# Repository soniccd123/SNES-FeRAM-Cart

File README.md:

# SNES FeRAM Cart
A Open Hardware SNES Cartridge with save capability

# What is that?
A repro cartridge PCB for SNES and Super Famicom consoles compatible with LoROM and HiROM software and save capability using FeRAM memory. Its a open hardware project and can be modified with no restriction

This project was possible thanks to poorstudenthobbyist (Very nice and informative guides) and whicker (Showed the basics of how to wire a FeRAM to SNES), as well as other members of NESdev forums.

# Why is that?
While there are very nice comercially available repro PCB solutions, these are closed solutions that often doesn't fit the needs of everyone, specially concerning availability of parts, so, making this project open is not only a way to give back to the community that helped me alot, but also to give the ones that need a more versitile way to solve their problems. I know that the way that this PCB was designed may not fit everyone, but i hope that the ability to modify this project as one needs solves this.

I also find the canibalization of original cartridges for making repros, while understandable in many cases, discusting, so, may this project help to curb this practice.

# Features as of now
- Suports SNES and Super Famicom
- ROM Support for up to 4MB
- HiROM and LoROM software (set by jumpers)
- 32KB of FeRAM for saving (256kb)
- No need for backup battery
- Rudimentary ROM bank switch (Permits multiple games on same ROM)
- SuperCIC support
- DOES NOT SUPPORT SPECIAL CHIP GAMES (while i would love to, this is quite away from my capacity as of now)

# Component List:
- 1x FM1808B;
- 1x 27C322 (May use other 27CXX memories with some minor modifications);
- 1x 74HC139 (or LS);
- 1x 4081;
- 1x 4071;
- 2x 74HC245;
- 1x SuperCIC (PIC12F629 model);
- 1x Led (Optional, only used for SuperCIC)
- 4x 1K Resistors (5x if using the LED with the SuperCIC);
- 1x 4 channel DIP Switch;
- 2x 10nF Capacitors;

# Technical details

This project was developed using KiCAD and can be easily modified and studied by using it. Terminals are left in the PCB for all cartridge port connections for testing, but these can easily be removed if wanted.

4081 and 4071 circuitry help to control backup RAM access and also permit FeRAM correctly reading and writing. If

While bank switching is present, its use is not absolutely required for the cart to work. In this case, the resistors are not needed, just short each SW1 channel (as if it were on). 

Also, while save capability is present, it is not required for the cart to work. 4071 and 4081 are still required in these cases

SuperCIC have been tested by other users and works. A SOIC8 footprint will be added aswell in the next commit for more package options.

# How to use

The ROMs to be written to the EPROM need to be headerless.

ROM type: HiROM and LoROM are selected by shorting the corresponding side of all the jumpers to the center, HiROM ones are annotated with H and LoROM with L.

Bank Switching: The user may write multiple roms to the same EPROM, the DIP switch controls which area of the EPROM is read by the SNES/Super Famicom; The minimum bank size is 256KB. Each of the switches connect a memory address line between the system and the EPROM: when the switch is on, the respective address line is controlled by the SNES; When off, the EPROM adress line is pulled-up and cut from SNES control. the address lines are A20, A19, A18, A17 (considering LSB as A0). To select the desired bank, turn the switches on and off acordingly to the begining address that the ROM occupies in the EPROM.

Examples:

ROM_x begin at 0x100000 -> Switch just A19 off (pull-up);           
ROM_y begin at 0x180000 -> Switch A19 and A18 off;

This technique may not be compatible with save supporting SNES/Super Famicom software.

How to make multirom file: Just use the CMD command "copy /b rom_x.bin + rom_y.bin + rom_z.bin rom_result.bin" to join them to one file. One may join how many ROMs he wants to, just be shure that the result file is smaller than the total size of the EPROM and that the ROMs fit correctly to each desired bank to make software switching possible.

# Disclaimer

I'm not an professional engineer and created this project as a hobby, this said, problems and errors maybe present and in need to be corrected. I'll try you to help the best as I can if any problems arrise but be aware that they may exist.

Happy playing!

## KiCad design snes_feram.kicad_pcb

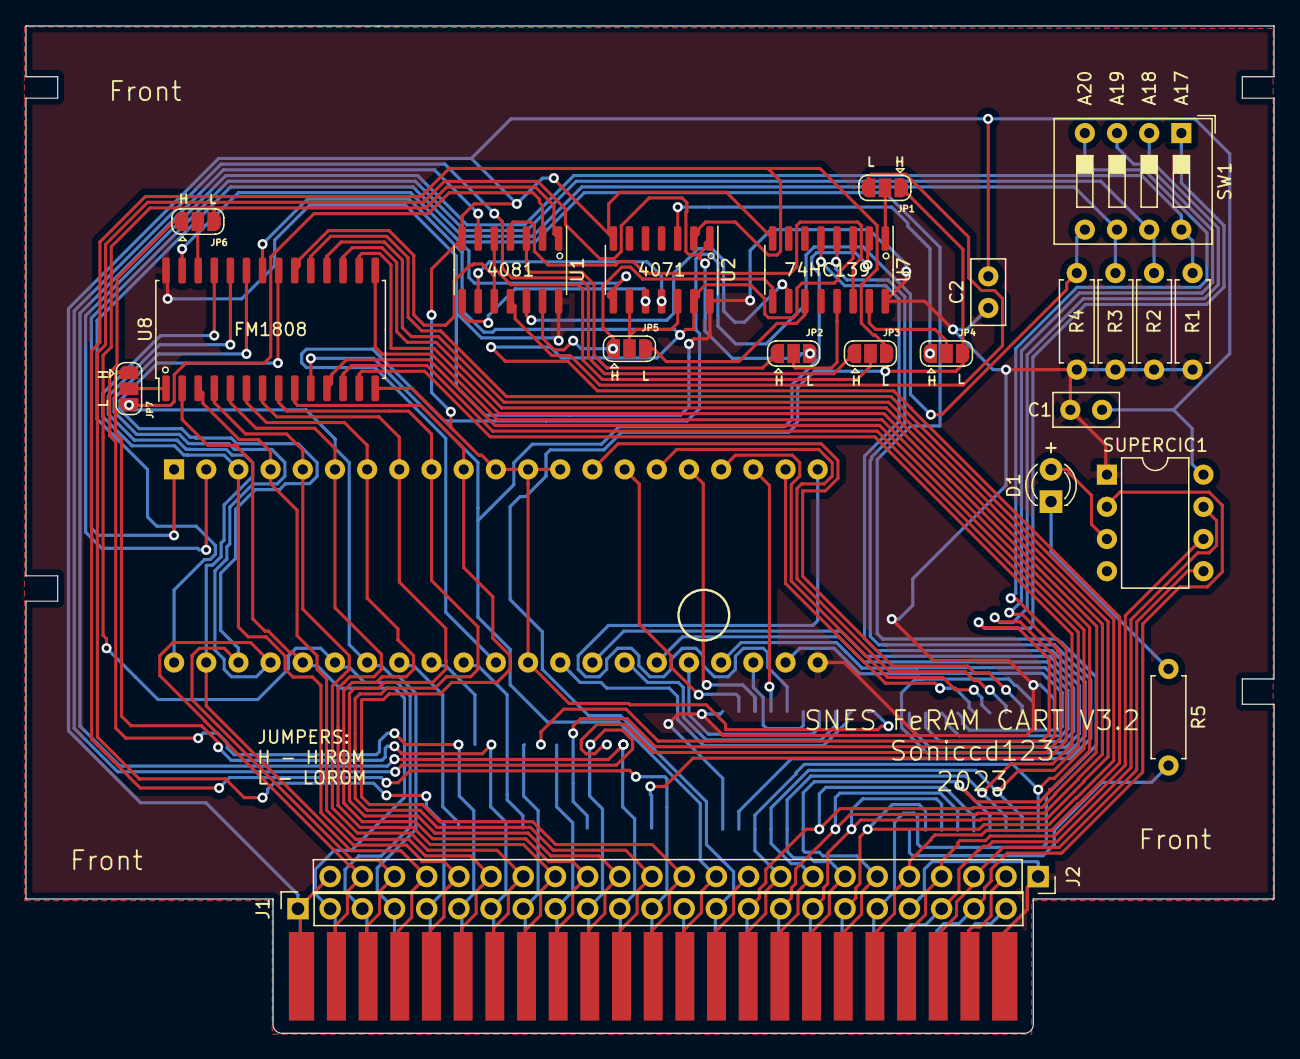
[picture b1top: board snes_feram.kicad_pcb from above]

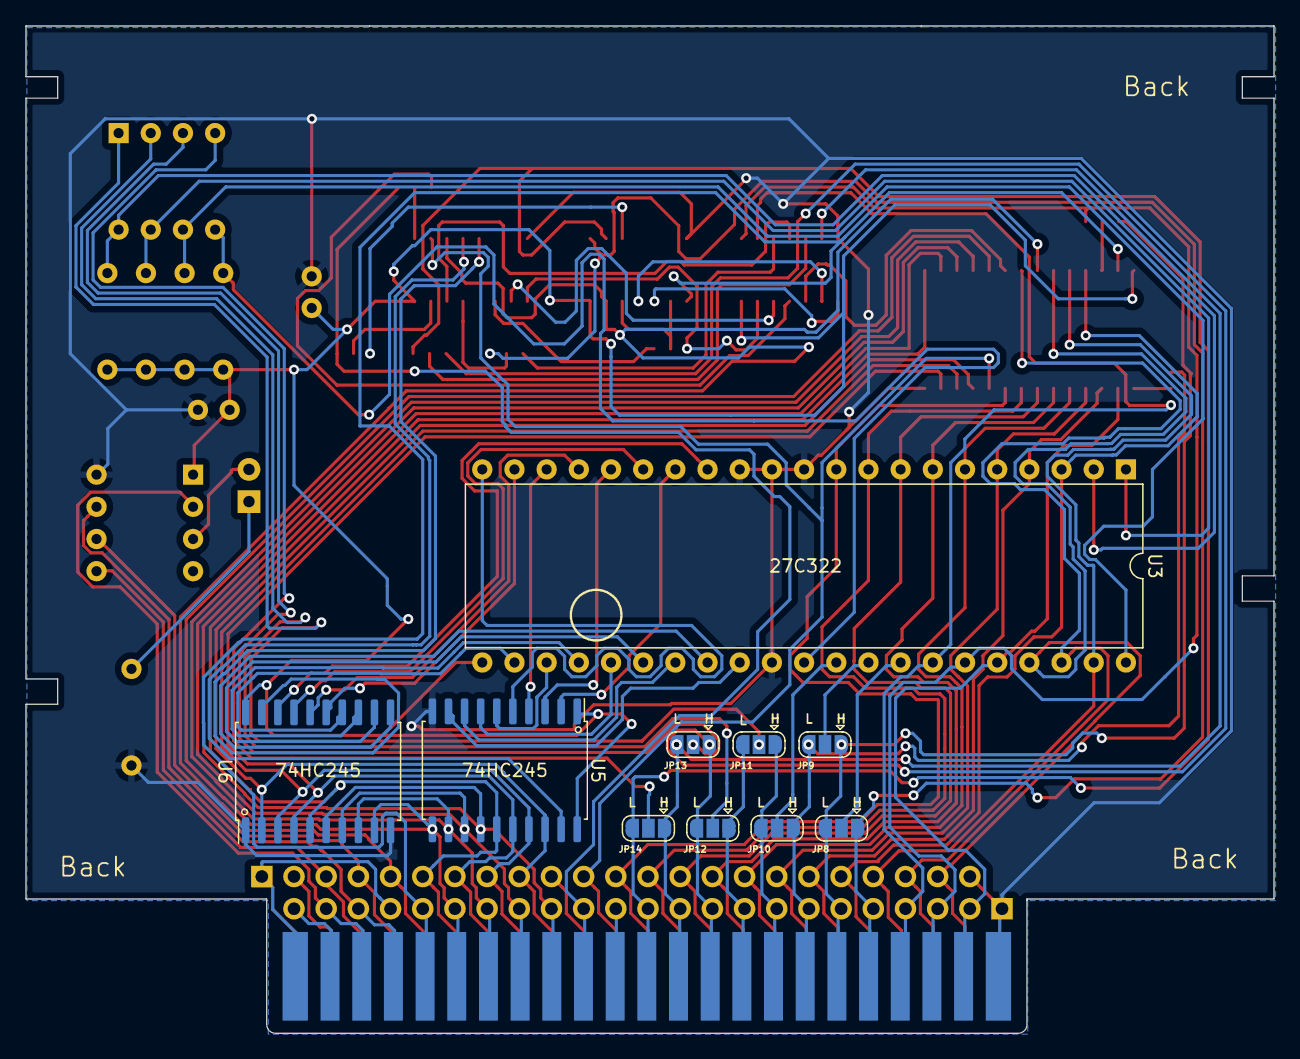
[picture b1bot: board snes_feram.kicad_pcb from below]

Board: 2 copper layers, 98.5 x 79.5 mm, 34 parts (10 on the bottom side), 90 nets.

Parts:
C1, C2: C; C_Disc_D5.0mm_W2.5mm_P2.50mm
CON1: SNES-EDGE; SNES-EDGE-Bigger
D1: LED; LED_D3.0mm
J1, J2: Conn_01x23_Male; PinSocket_1x23_P2.54mm_Vertical
JP1, JP2, JP3, JP4, JP5, JP6, JP7, JP8, JP9, JP10, JP11, JP12, JP13, JP14: SolderJumper_3_Open; SolderJumper-3_P1.3mm_Open_RoundedPad1.0x1.5mm
R1, R2, R3, R4: R; R_Axial_DIN0207_L6.3mm_D2.5mm_P7.62mm_Horizontal
R5: 1K; R_Axial_DIN0207_L6.3mm_D2.5mm_P7.62mm_Horizontal
SUPERCIC1: PIC12F629-IMC; DIP-8_W7.62mm
SW1: SW_DIP_x04; SW_DIP_SPSTx04_Slide_9.78x12.34mm_W7.62mm_P2.54mm
U1: 4081; SOIC-14_3.9x8.7mm_P1.27mm
U2: 4071; SOIC-14_3.9x8.7mm_P1.27mm
U3: 27C322; DIP-42_W15.24mm
U5, U6: 74LS245; SOIC-20W_7.5x12.8mm_P1.27mm
U7: 74LS139; SOIC-16_3.9x9.9mm_P1.27mm
U8: FM18W08-SG; SOIC-28W_7.5x17.9mm_P1.27mm

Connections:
+5V: C1.1, C2.1, CON1.27, CON1.58, J1.20, J2.1, R1.1, R2.1, R3.1, R4.1, SUPERCIC1.1 (VDD), U1.14 (VDD), U2.14 (VDD), U3.22 (VCC), U5.1 (A->B), U5.20 (VCC), U6.20 (VCC), U7.16 (VCC), U8.28 (VDD)
/A0: CON1.16, J2.12, U3.10 (A0), U8.9 (A1)
/A1: CON1.15, J2.13, U3.9 (A1), U8.8 (A2)
/A2: CON1.14, J2.14, U3.8 (A2), U8.7 (A3)
/A3: CON1.13, J2.15, U3.7 (A3), U8.6 (A4)
/A4: CON1.12, J2.16, U3.6 (A4), U8.5 (A5)
/A5: CON1.11, J2.17, U3.5 (A5), U8.4 (A6)
/A6: CON1.10, J2.18, U3.4 (A6), U8.3 (A7)
/A7: CON1.9, J2.19, U3.3 (A7), U8.25 (A8)
/A8: CON1.8, J2.20, U3.41 (A8), U8.24 (A9)
/A9: CON1.7, J2.21, U3.40 (A9), U8.21 (A10)
/A10: CON1.6, J2.22, U3.39 (A10), U8.23 (A11)
/A11: CON1.37, J1.2, U3.38 (A11), U8.2 (A12)
/A12: CON1.38, J1.3, JP6.3 (B), U1.1, U3.37 (A12)
/A13: CON1.39, J1.4, JP7.3 (B), U1.2, U3.36 (A13)
/A14: JP8.2 (C), U3.35 (A14)
/A15: JP9.2 (C), U3.34 (A15)
/A16: JP10.2 (C), U3.33 (A16)
/A17: JP11.2 (C), SW1.1
/A17_ROM: R1.2, SW1.8, U3.2 (A17)
/A18: JP12.2 (C), SW1.2
/A18_ROM: R2.2, SW1.7, U3.1 (A18)
/A19: JP13.2 (C), SW1.3
/A19_ROM: R3.2, SW1.6, U3.42 (A19)
/A20: JP14.2 (C), SW1.4
/A20_ROM: R4.2, SW1.5, U3.32 (A20)
/BA7: CON1.48, J1.13
/BYTE: CON1.17, J2.11, U7.2 (A0), U8.10 (A0)
/BYTE_0: U6.19 (CE), U7.4 (O0)
/BYTE_1: U5.19 (CE), U7.5 (O1)
/CART_D0: CON1.19, J2.9, U5.18 (B0), U6.2 (A0), U8.11 (DQ0)
/CART_D1: CON1.20, J2.8, U5.17 (B1), U6.3 (A1), U8.12 (DQ1)
/CART_D2: CON1.21, J2.7, U5.16 (B2), U6.4 (A2), U8.13 (DQ2)
/CART_D3: CON1.22, J2.6, U5.15 (B3), U6.5 (A3), U8.15 (DQ3)
/CART_D4: CON1.50, J1.15, U5.14 (B4), U6.6 (A4), U8.16 (DQ4)
/CART_D5: CON1.51, J1.16, U5.13 (B5), U6.7 (A5), U8.17 (DQ5)
/CART_D6: CON1.52, J1.17, U5.12 (B6), U6.8 (A6), U8.18 (DQ6)
/CART_D7: CON1.53, J1.18, U5.11 (B7), U6.9 (A7), U8.19 (DQ7)
/CIC_CLK: CON1.56, J1.22, SUPERCIC1.2 (GP5)
/CIC_IN: CON1.55, J1.21, SUPERCIC1.7 (GP0)
/CIC_OUT: CON1.24, J2.4, SUPERCIC1.6 (GP1)
/CIC_RST: CON1.25, J2.3, SUPERCIC1.5 (GP2)
/CPU_CLK: CON1.57, J1.23
/D0: U3.14 (D0), U6.18 (B0)
/D1: U3.16 (D1), U6.17 (B1)
/D2: U3.18 (D2), U6.16 (B2)
/D3: U3.20 (D3), U6.15 (B3)
/D4: U3.23 (D4), U6.14 (B4)
/D5: U3.25 (D5), U6.13 (B5)
/D6: U3.27 (D6), U6.12 (B6)
/D7: U3.29 (D7), U6.11 (B7)
/D8: U3.15 (D8), U5.2 (A0)
/D9: U3.17 (D9), U5.3 (A1)
/D10: U3.19 (D10), U5.4 (A2)
/D11: U3.21 (D11), U5.5 (A3)
/D12: U3.24 (D12), U5.6 (A4)
/D13: U3.26 (D13), U5.7 (A5)
/D14: U3.28 (D14), U5.8 (A6)
/D15: U3.30 (D15), U5.9 (A7)
/EDGE_A15: CON1.40, J1.5, JP2.3 (B), JP8.1 (A), U2.1
/EDGE_BA0: CON1.41, J1.6, JP6.1 (A), JP8.3 (B), JP9.1 (A)
/EDGE_BA1: CON1.42, J1.7, JP7.1 (A), JP9.3 (B), JP10.1 (A)
/EDGE_BA2: CON1.43, J1.8, JP10.3 (B), JP11.1 (A)
/EDGE_BA3: CON1.44, J1.9, JP11.3 (B), JP12.1 (A)
/EDGE_BA4: CON1.45, J1.10, JP3.1 (A), JP12.3 (B), JP13.1 (A)
/EDGE_BA5: CON1.46, J1.11, JP13.3 (B), JP14.1 (A), U1.6
/EDGE_BA6: CON1.47, J1.12, JP3.3 (B), JP14.3 (B), U2.2
/RAM_CE: U1.10, U8.20 (~CE)
//CART: J1.14, JP1.1 (A), JP4.3 (B)
//RD: J2.5, U2.13, U7.3 (A1), U8.22 (~OE)
//WR: J1.19, U2.8, U8.27 (~WE)
GND: C1.2, C2.2, CON1.5, CON1.36, J1.1, J2.23, R5.2, SUPERCIC1.8 (VSS), U1.7 (VSS), U2.7 (VSS), U3.11 (~E), U3.12 (GND), U3.13 (~GVPP), U3.31 (GND), U5.10 (GND), U6.1 (A->B), U6.10 (GND), U7.8 (GND), U8.14 (VSS)
unnamed: D1.1 (K), R5.1
unnamed: D1.2 (A), SUPERCIC1.3 (GP4)
unnamed: JP1.2 (C), U7.1 (E)
unnamed: JP1.3 (B), U1.11
unnamed: JP2.1 (A), U1.3
unnamed: JP2.2 (C), U7.13 (A1)
unnamed: JP3.2 (C), U1.5
unnamed: JP4.1 (A), U2.3
unnamed: JP4.2 (C), U7.15 (E)
unnamed: JP5.1 (A), U1.13, U7.9 (O3)
unnamed: JP5.2 (C), U2.9, U2.12
unnamed: JP5.3 (B), U7.11 (O1)
unnamed: JP6.2 (C), U8.26 (A13)
unnamed: JP7.2 (C), U8.1 (A14)
unnamed: U1.4, U7.14 (A0)
unnamed: U1.8, U2.10
unnamed: U1.9, U2.11
unnamed: U1.12, U7.10 (O2)

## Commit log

2020-10-26 Parts annotated
2020-10-26 Create README.md
    Added details to project
2020-10-26 Forgot to add protection resistor to LED
2020-10-26 Updated Gerber files
2020-11-02 EPROM is now on the back of PCB for better shell fit; Silkscreen mark for shell contact points corrected
2020-11-02 Small change on silkscreen
2020-11-02 Gerber updated with last changes
2021-02-24 Corrected missing trace at pin 20 of U5, thanks to @DeLFuS
2023-09-01 -Upgrade to kicad6 -Fixed ERC errors -Edited soic footprints to indicate pin1 with a circle -Added Slash to Low asserted signals -Fixed byte swapping
2023-09-01 -Fixed footprint library missing -Updated soic footprints -Updated version number
